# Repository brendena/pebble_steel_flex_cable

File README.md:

# pebble steel flex cable
This is a atempt to figure out whats on the pebble steel flex cable.  But I'm not a electrical engineer.  So some things might be a little off.

## Parts
I don't know for sure what the exact parts are.  But these seem tobe matching up very nicely.  The Ic on the top responds the exact same way as the IS31FL3199.  

* [IS31FL3199](https://www.digikey.com/en/products/detail/lumissil-microsystems/IS31FL3199-QFLS2-TR/4286437?utm_adgroup=&utm_source=google&utm_medium=cpc&utm_campaign=Pmax_Shopping_Boston%20Metro%20Category%20Awarness&utm_term=&utm_content=&utm_id=go_cmp-20837509568_adg-_ad-__dev-c_ext-_prd-4286437_sig-Cj0KCQjw5cOwBhCiARIsAJ5njuZyUMDJUlp2XiBO9IcWK7s09v9mx462ozWoL-kYqcOZMEzYlfcLx_4aAvgXEALw_wcB&gad_source=1) - LED driver
* [molex 5055511620](https://www.digikey.com/en/products/detail/molex/5055511620/10127964) 16 pin board connector.  Should be the same as in the pebble original.

## other post
* [original pebble watch](https://www.reddit.com/r/pebble/comments/10hv3ih/pebble_classic_flex_schematic/)

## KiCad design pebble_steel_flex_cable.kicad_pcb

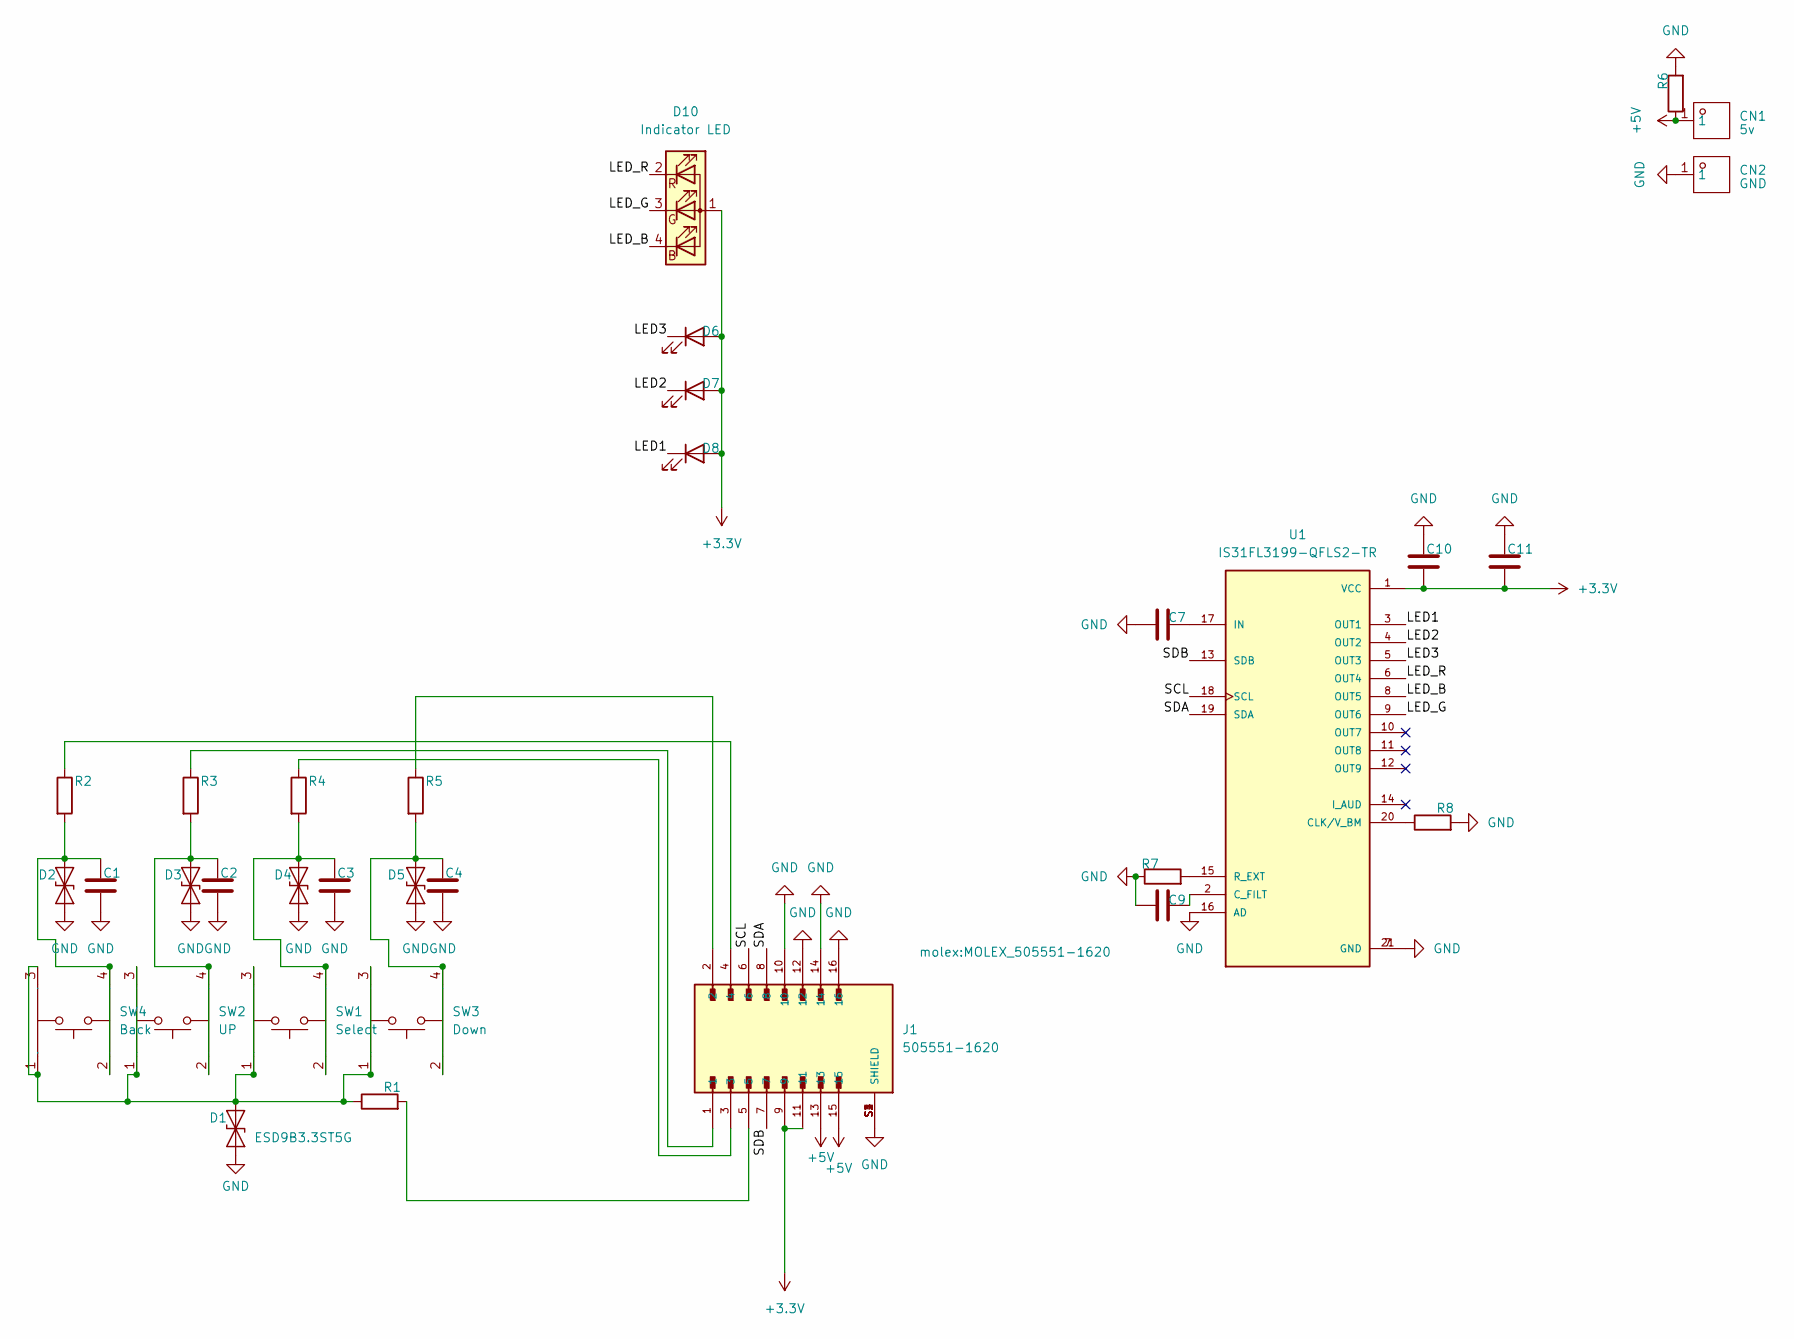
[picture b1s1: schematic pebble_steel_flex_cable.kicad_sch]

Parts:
C1, C2, C3, C4, C7, C9, C10, C11: C; C_0201_0603Metric
CN1: 5v; SMD_L2.7-W1.5; Manufacturer Part S7121-42R
CN2: GND; SMD_L2.7-W1.5; Manufacturer Part S7121-42R
D1, D2, D3, D4, D5: ESD9B3.3ST5G; D_SOD-923
D6, D7, D8: LED; LTW-020ZDCG
D10: Indicator LED; led_SML-LX0404SIUPGUSB
J1: 505551-1620; MOLEX_505551-1620; PARTREV B
R1, R2, R3, R4, R5, R6, R7, R8: R; R_0201_0603Metric
SW1: Select; SW-SMD_SKSHAAE010; Manufacturer Part SKSHAAE010
SW2: UP; SW-SMD_SKSHAAE010; Manufacturer Part SKSHAAE010
SW3: Down; SW-SMD_SKSHAAE010; Manufacturer Part SKSHAAE010
SW4: Back; SW-SMD_SKSHAAE010; Manufacturer Part SKSHAAE010
U1: IS31FL3199-QFLS2-TR; QFN40P300X300X80-21N; PARTREV B

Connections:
+3.3V: C10.1, C11.1, D6.2 (A), D7.2 (A), D8.2 (A), D10.1 (A), J1.9, J1.11, U1.1 (VCC)
+5V: CN1.1, J1.13, J1.15, R6.1
/LED1: D8.1 (K), U1.3 (OUT1)
/LED2: D7.1 (K), U1.4 (OUT2)
/LED3: D6.1 (K), U1.5 (OUT3)
/LED_B: D10.4 (BK), U1.8 (OUT5)
/LED_G: D10.3 (GK), U1.9 (OUT6)
/LED_R: D10.2 (RK), U1.6 (OUT4)
/SCL: J1.6, U1.18 (SCL)
/SDA: J1.8, U1.19 (SDA)
/SDB: J1.7, U1.13 (SDB)
GND: C1.2, C2.2, C3.2, C4.2, C7.1, C9.2, C10.2, C11.2, CN2.1, D1.1 (A1), D2.1 (A1), D3.1 (A1), D4.1 (A1), D5.1 (A1), J1.10, J1.12, J1.14, J1.16, J1.S1 (SHIELD), J1.S2 (SHIELD), J1.S3 (SHIELD), J1.S4 (SHIELD), R6.2, R7.1, R8.2, U1.7 (GND), U1.16 (AD), U1.21 (GND)
unnamed: D1.2 (A2), R1.1, SW1.1, SW1.3, SW2.1, SW2.3, SW3.1, SW3.3, SW4.1, SW4.3
unnamed: C1.1, D2.2 (A2), R2.2, SW4.2, SW4.4
unnamed: C2.1, D3.2 (A2), R3.2, SW2.2, SW2.4
unnamed: C3.1, D4.2 (A2), R4.2, SW1.2, SW1.4
unnamed: C4.1, D5.2 (A2), R5.2, SW3.2, SW3.4
unnamed: J1.1, R3.1
unnamed: J1.2, R5.1
unnamed: J1.3, R4.1
unnamed: J1.4, R2.1
unnamed: J1.5, R1.2
unnamed: R8.1, U1.20 (CLK/V_BM)
unnamed: C9.1, U1.2 (C_FILT)
unnamed: C7.2, U1.17 (IN)
unnamed: R7.2, U1.15 (R_EXT)

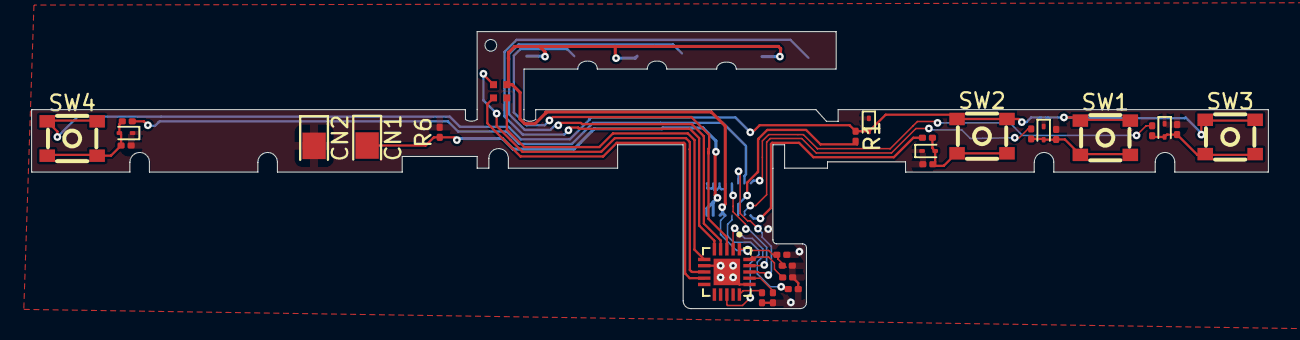
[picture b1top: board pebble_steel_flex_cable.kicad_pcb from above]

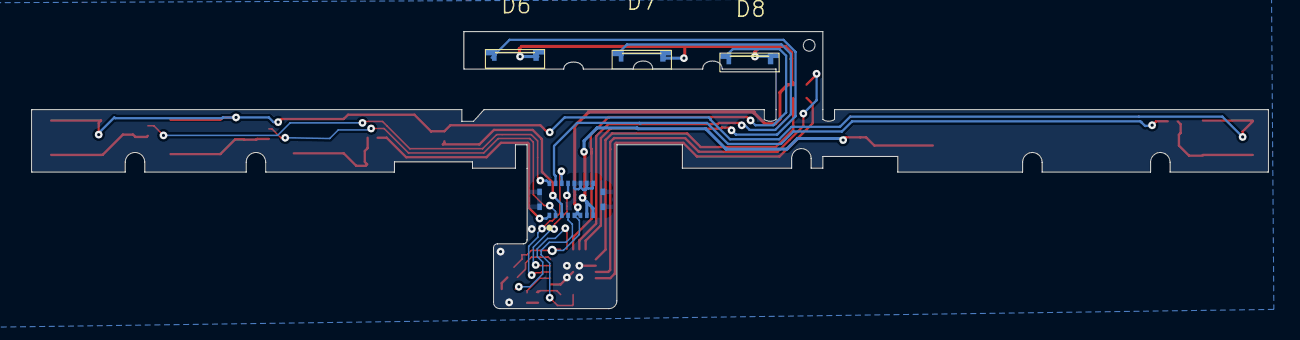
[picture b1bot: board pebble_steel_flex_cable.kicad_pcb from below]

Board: 2 copper layers, 79.2 x 17.8 mm, 33 parts (4 on the bottom side), 26 nets.

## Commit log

2024-05-08 start of figuring out the cable
2024-05-09 most of its mapped out
2024-05-14 added some images of the cable
2024-05-17 fixed the layout and added the doc for the part
2024-05-17 added image
2024-05-17 added a pdf output
2024-07-07 started layout
2024-07-07 added the buttons and the battery connections
2024-07-07 added the LED part
2024-07-16 added flat bed scans
2024-08-11 added the start of the flex cable layout
2024-08-11 added changes
2024-08-11 got the outline almost there
2024-08-13 got the flex layed out
2024-08-14 send for fit test
2025-10-15 not sure what changed
